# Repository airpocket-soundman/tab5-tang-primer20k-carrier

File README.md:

# Tab5 × Tang Primer 20K 接続キャリア基板

2026-11-08：FPGA単独推論の実験版4E30を追加。FPGA内RV32IMCが量子化・正規化等を処理し、共通INT8 MACが積和演算を担当する。Tab5/P4はモデル・画像の搬入と表示のみ。全RT-DETR649演算は実RV32 ISA試験で完走し、実機では14整数のCPU＋MAC試験に合格。**全モデルの実機完走・速度は未確認**。[自律実行仕様](docs/NPU_AUTONOMOUS_V1.md)、[ISA検証](docs/NPU_AUTONOMOUS_RV32_ISA_2026-11-08.md)を参照。Linux/MeOS loaderは未実装。

2026-11-07：NPU DDR診断版4E21で、YOLO S256の32MiB超え実行と、学習済みDeiT-tiny全12ブロック・74行列演算の実機実行を確認。Transformerの1000出力は同じP4の独立CPU整数計算と全ビット一致した。既存の積和回路を使い、ピン・通信コマンドの変更はない。非線形演算等はP4が担当し、Linux/MeOSへのホスト実装移植とSTA収束は未完了。[Transformer実機記録](docs/NPU_Transformer_実機検証_2026-11-07.md)、[DDR MatMul検証](docs/NPU_DDR_MatMul_検証_2026-11-07.md)を参照。

2026-11-06の保存点：GPU全8シーン/TX40・RX16検証記録とMEM DMA検証・復元資料をmainへ統合。[当時の現在地・全host適合範囲・整理方針](docs/INTEGRATION_2026-11-06.md)を参照。RX20、長時間soak、DDR付きGFXは未完了。

M5Stack Tab5のM5-BusとTang Primer 20K Coreを接続する専用キャリア基板の設計リポジトリです。

## 状態

2026-11-05のジャンパ接続GFX実機では、全8シーン×3負荷の640×360画像照合とFlow継続照合に合格。
[全8シーンの仕様・実績・失敗候補](docs/GFX全8シーン拡張_2026-11-05.md)を参照。
現行SLogic配線はCLK=D7／DIR=D6／READY=D4／DATA0～7=D15～D8で、
[9往復CRC照合による全チャンネル特定記録](fpga/validation/probe-map-complete-2026-11-05/manifest.json)を保存した。
これはジャンパ実機の結果であり、下記キャリア基板の製造・検証完了を意味しない。

フル125×78mmと廉価版A99×78mmの設計レビュー用データがあります。未製造・未実機検証です。

**実装仕様変更（2026-10-26）：** 片面SMTを優先し、主電源スイッチと旧FPGA専用停止SW3を省くr4へ変更しました。Tab5用J3はLCSC別購入・手はんだです。設計側PCB DRC違反・ERCエラーは両版とも0です。ERC警告はフル版163件、廉価版164件（ライブラリシンボル不一致160／161件と孤立ピンラベル3件）あります。EasyEDA反映・再計算完了のため見積もり用で、製造リリースは未完了です。[現在の仕様](spark/single-sided-r4/README.md)。

## 保持している従来版

125×78mmの従来版と廉価版A/B/Cは保存しています。既存の製造・解析記録は各版のものです。Spark主電源改訂の検証結果ではありません。

- [廉価版3案の一覧](variants/README.md)
- [3案の共通設計仕様](variants/DESIGN_SPEC.md)
- [廉価版レポート](site/lite-variants.html)

## 設計の起点

[共通ハードウェア仕様・設計チェック項目](docs/ESP32P4_FPGA_共通ハード仕様.md)

- 初期通信：8bit PARLIOと制御線。将来16bit化を検討。
- 電源：外部約12VからTab5 HVINへ供給し、FPGAには独立した12V→5V DC-DCで供給。
- 共通GNDとし、Tab5の5VレールとFPGA用5Vは直結しない。
- DDR3はCore搭載のものを使用する。

GPIO割り当て・コネクタ・電源条件は暫定です。一次資料との照合、I/O電圧・競合・起動状態・逆給電の確認を行い、仕様のチェック項目を完了してから製造に進みます。

## FPGAデバイスと利用するホスト

Tab5側のソフト実装は[ホストソフト開発ガイド](docs/Tab5ホストソフト開発ガイド.md)を参照してください。

ジャンパ線で先に通信・描画を試す場合は[Dock接続とTab5内蔵LCDのGFX試験手順](docs/Dockジャンパ_GFXテスト手順.md)を参照。Dock用top、32×32 RGB565描画診断、読み戻し照合とホスト側表示経路を開発しています。RTL試験とOSSでの合成・配置配線・ビットストリーム生成は成功、Gowin EDAと実機は未検証です。

本リポジトリは、キャリア基板と、その上で動くFPGAデバイス（全ビットストリーム）を一元管理します。ホストOSの各リポジトリは本リポジトリの仕様を参照してホスト側を開発します。[リポジトリ分担と参照ルール](docs/リポジトリ分担と参照ルール.md)、[FPGAデバイス構成](docs/FPGAデバイス構成_ビットストリームと機能.md)、[fpga/](fpga/README.md)を参照してください。

| リポジトリ | ホスト側の役割 |
|---|---|
| [tab5-linux-fpga](https://github.com/airpocket-soundman/tab5-linux-fpga) | NOMMU Linux本体、FPGA通信ドライバ、Device Tree、ユーザ空間ツール |
| [tab5-meos-fpga](https://github.com/airpocket-soundman/tab5-meos-fpga) | MeOSのFPGAドライバ（HAL/LL PARLIO）、GUI統合 |
| [tab5-fpga-gpu](https://github.com/airpocket-soundman/tab5-fpga-gpu) | ESP-IDFのホスト実装、ベンチマーク（GPU LAB）、モデル評価 |
| [esp32p4-linux-fpga-memory](https://github.com/airpocket-soundman/esp32p4-linux-fpga-memory) | Linux外部メモリ研究の計画・評価 |

FPGAの機能（GFX、NPU、HDMI、RAMdisk）はどのホストOSからも使う前提です。ビットストリームは機能別に分け、同時搭載は計測で問題がない組合せに限ります。

Linux側では双方向のコマンド・データ転送、128MB DDR3全域への分割読み書き、フロー制御・通知とエラー検出を支えます。描画用途では描画コマンド送信と完成フレーム受信を支え、640×360 RGB565・30FPSの目標に対して、フレーム本体だけで約13.8MB/sを要する受信経路を評価します。DMA対応と実効帯域は未検証であり、性能を保証するものではありません。

共通仕様・デバイス仕様の更新は本リポジトリを起点とし、ホスト側リポジトリに収録した仕様コピーへ反映してください。

## Spark応募用の独立フル機能版

従来設計とA/B/Cの計画を保持し、125×78mm・HDMI・USB PD付きの別版を [spark/](spark/README.md) で開発しています。KiCadで設計・解析してEasyEDAへ移植し、PCBAを優先、手はんだ品もLCSC調達を優先し、適合品をLCSCで調達できない場合のみ秋月電子へ集約します。[検証状況と残件](spark/design/VERIFICATION_STATUS.md)を確認してください。現行の製造データは見積・レビュー用です。

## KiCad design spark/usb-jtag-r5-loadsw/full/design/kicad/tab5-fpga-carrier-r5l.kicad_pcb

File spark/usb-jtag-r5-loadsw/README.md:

# r5l：SW4を信号専用にして、+5VをPMOSのロードスイッチで通す変種（PoC・発注候補）

2026-11-06。**実機未検証。リリースではありません。** r5s（`../usb-jtag-r5-switch/`）の派生で、r5s、r5、r5c、r4 のファイルは変更していません。

## 何を変えたか

- r5sでは、SW4（G-Switch SS-23D03-G080）が+5Vレールの電流を通していた。この部品の電流定格は、メーカーのデータシートで **0.3A・50V DC**（LCSCの掲載値1Aと食い違う）。
- r5lでは、SW4は**信号だけ**（ゲート駆動とCFG1）。+5Vの電流は、背中合わせのPMOS（AO3401A）が通す。
  - RUN経路 Q11・Q12（BUCK_5V → +5V）、PGM経路 Q13・Q14（VBUS_PD → +5V）。
  - PGM経路の過電圧ガード Q15・D12・R95（VBUS_PDが約7Vを超えたら、PGM経路をオフにする）。
- 追加11部品（Q11〜Q15、D12、R91〜R95）。基板の部品位置・配線の他の部分は、r5sのまま。

詳しい検討・SPICE結果・未確認事項は `../../docs/r5s_SW4ロードスイッチ式の検討_2026-11-06.md`。

## 中身

| 場所 | 内容 |
|---|---|
| `full/design/kicad/` | KiCadの回路図・基板・BOM・回路契約（`circuit-contract.json`）。`gen/` に生成スクリプト |
| `full/design/kicad/gen/add_loadsw.py` | r5sの基板から、r5lの基板を作る（部品の配置探索＋配線）。`loadsw_routes.py` が配線の指定 |
| `sim-spice/` | ロードスイッチのngspice検証（`run_all.py`、結果は `results.json`）。汎用モデル |
| `verify_design.py` | 回路図のネットリスト検査（SW4の位置モデル、ロードスイッチの接続、SW4が電源を通さないこと、ERC・DRC） |
| `order/` | JLCPCB向けの発注候補データ（ガーバー、BOM、CPL）と、`README.md`（未解決事項） |
| `review/` | 確認用の画像（3D） |

## 検証したこと

- ERCエラー0、PCB DRC違反0、未配線0（`full/design/kicad/sim/`）。
- 回路図と基板のネット照合: 761ピン、不一致0。r5sとの基板の差分は、SW4の電源配線の削除24点と、SW4の3ピンのネット変更だけ。
- `verify_design.py`: PASS（SW4のスライダ位置モデル、ロードスイッチの接続、危険な組合せなし）。
- SPICE（汎用モデル）: RUN／PGM／OFF、DCのみ、VBUS 12V誤使用（+5V＝0V）、5.5V給電で誤遮断なし。+5Vのピークは、ランプで5.5〜7.7V。

## 既知の制約（PoCとして受け入れる範囲）

2026-11-07の再監査（`../../docs/r5l基板再監査_2026-11-07.md`）を受けて、次を明記する。

1. **過電圧ガードは、定格内に収める保護ではない。** VBUSがランプで上がるとき、+5Vのピークは最大約7.7Vで、**3.3V LDO（U3 TLV1117LV33）の絶対最大入力6V（動作範囲は2〜5.5V）を超える**。ガードは、12VのままPGMへ切り替えるなどの誤使用で、被害を小さくする「保険」にとどまる。約7Vで切る6.2Vゼナー方式は、PDの5V許容（5.5V）を通しつつ5.5V超を切る、という窓に原理的に合わない。回路は、PoCとして作り直さない。
2. **運用ルール:** RUN／OFF／PGM（SW4）と、JP3、JP1の切り替えは、**電源アダプタとUSB-Cを外した無電源の状態で行う**（シルクの `POWER OFF!` のとおり）。通電中のモード切替は、保護の対象に入れていない。
3. **USB D+／D−:** 差動ペアとして並べて配線していない。経路長はD+約17.0〜17.5mm、D−約25.1〜27.0mm（差約8mm）。90Ωの積層設計も未確認。ハイスピード動作は、実機で確認する（ハイスピードで認識できない場合は、フルスピードの動作を確認する）。

### Core（Tang Primer 20K）のI/O電源（VCCO）の条件

このキャリアは、SODIMMの164・166（Bank 0/1の外部VCCO）と、170・174（Bank 7の外部VCCO）を**未接続**にしている。一方で、Bank 0、1、7のピンを使う（Bank 7には、LINKの F_D5、F_D6、F_D7、F_DIR などが載る）。

- Core回路図の読み取り（`../../docs/reference/README.md`、`../../docs/Dockジャンパ試験_配線とFPGA構成_2026-10-28.md`）では、**既定のCoreは R5（Bank 0/1）と R9（Bank 7）が付いていて、VCCOはCore内部の3.3V**。この場合、164・166・170・174を未接続にしても、該当バンクは3.3Vで動く。
- **R6（Bank 0/1の外部選択）または R13（Bank 7の外部選択）が付いているCoreでは、キャリアがVCCOを供給しない限り、該当バンクが無給電になる。**
- 公式Dockは、164・166に3.3Vを接続し、170・174は未接続にしている（Bank 7は、Dock上でR9の実装を確認できないため、使わない運用）。**Dockで動いたことは、このキャリアでBank 7が動く証拠にならない。**

**このキャリアで使うCoreの条件（組立・受入）:**
1. R5とR9が実装されていて、R6とR13が実装されていないこと。Coreを挿す前に、実物で目視（または抵抗の導通）で確認する。
2. Coreに5Vだけを与えて通電した状態（キャリアには挿さない、またはキャリアの5Vだけ入れる）で、**Core基板上の VCCO7 のノード（R9またはR13の、FPGA側のパッド、またはFPGA近くのVCCO7のデカップリング容量）とGNDの間の電圧が3.3Vであること**を確認する。**SODIMMの170・174の電圧では、確認できない**（R13が実装されていなければ、170・174はCoreの内部にどこにもつながらず、電圧が出ない。R9実装・R13非実装が、この基板の想定する正しい状態）。同様に Bank 0/1 は、R5またはR6のFPGA側パッドで確認する。
3. 確認できていない間は、「Bank 7（F_D5〜F_D7、F_DIR、GPIO0〜4、F_LED0〜1 など）の動作は未確認」として扱う。

この条件は、実機のCoreで確認するまで、**未確認**である。

## 再現

```
"C:/Program Files/KiCad/10.0/bin/python.exe" full/design/kicad/gen/add_loadsw.py      # r5s基板 -> r5l基板
python full/design/kicad/gen/build_r5.py                                               # 回路図・BOM（r5lのコピー内でだけ実行）
python verify_design.py
python sim-spice/run_all.py
```

発注データの再生成は、`order/README.md` の「再生成」を参照。

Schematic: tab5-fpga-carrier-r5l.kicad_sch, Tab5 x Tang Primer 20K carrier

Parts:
C1: 100u/35V; CP_Elec_6.3x7.7; LCSC C2983388
C2: 1u/50V; C_0603_1608Metric; LCSC C15849
C3: 10n; C_0603_1608Metric; LCSC C57112
C4, C5: 10u/50V; C_1206_3216Metric; LCSC C13585
C6: 100n/50V; C_0603_1608Metric; LCSC C14663
C7: 220u/10V POSCAP; CP_EIA-7343-40_Kemet-Y; LCSC C242173
C8, C9: 47u/10V; C_1206_3216Metric; LCSC C96123; not fitted
C10: 10u/16V; C_1206_3216Metric; LCSC C13585
C11: 22u/10V; C_1206_3216Metric; LCSC C12891
C12, C13, C14, C15, C16, C17, C18, C19: 100n; C_0402_1005Metric; LCSC C1525
C20, C21, C22, C23, C24, C85, C88, C89, C90, C91, C92, C93, C94, C95, C97: 100n; C_0603_1608Metric; LCSC C14663
C86, C87: 33p; C_0603_1608Metric; LCSC C1663
C96: 4.7u; C_0603_1608Metric; LCSC C19666
D1, D2, D4: SS54; D_SMA; LCSC C22452
D3: SMBJ15A; D_SMB; LCSC C699013
D5, D6, D7, D8: LED; LED_0603_1608Metric; LCSC C2286
D10, D11: PESD5V0U1BL; D_SOD-882; LCSC C3001955
D12: BZT52C6V2; D_SOD-123; LCSC C19077403
F1: PTC 3A hold; Fuse_1812_4532Metric; LCSC C47002391
F2: PTC 500mA; Fuse_1206_3216Metric; LCSC C315893
H1, H2, H3, H4, H5, H6: M3; MountingHole_3.2mm_M3
J1: DC-005-5A-2.0; BarrelJack_XKB_C381116; LCSC C381116
J2: TYPE-C-31-M-12 USB2 + PD; USB_C_Receptacle_HRO_TYPE-C-31-M-12; LCSC C165948
J3: 2.54-2*15P; PinHeader_2x15_Tab5_Bottom; LCSC C56496
J4: SOCKET XDAP-4042044-20401; DDR3_XDAP_4042044_20401; LCSC C22471982
J5: HDMI OUT; HDMI_A_Molex_208658-1001_Horizontal; LCSC C916313
J6: PMOD1; PinHeader_2x06_P2.54mm_Vertical; not fitted
J7: PMOD2; PinHeader_2x06_P2.54mm_Vertical; not fitted
J8: GPIO pads; PinHeader_1x09_P2.54mm_Vertical; not fitted
JP1: BUS ARM; PinHeader_1x03_P2.54mm_Vertical; LCSC C49257
JP3: MODE TAB5; PinHeader_1x03_P2.54mm_Vertical; LCSC C49257
L1: 15u/4A; L_Bourns_SRR1260; LCSC C2041333
Q1, Q2, Q3, Q4, Q7, Q8: 2N7002; SOT-23; LCSC C8545
Q5: MMBT3904; SOT-23; LCSC C20526
Q11, Q12, Q13, Q14, Q15: AO3401A; SOT-23; LCSC C15127
R1, R2, R5: 0R; R_0603_1608Metric; LCSC C21189
R4, R17, R18, R25: 0R; R_0603_1608Metric; LCSC C21189; not fitted
R6, R36, R37, R52, R82, R86, R87, R90, R95: 10k; R_0603_1608Metric; LCSC C25804
R7: 3.24k; R_0603_1608Metric; LCSC C22994
R8, R41, R47, R48, R73, R74, R88, R91, R93: 100k; R_0603_1608Metric; LCSC C25803
R9: 15k; R_0603_1608Metric; LCSC C22809
R10, R11, R12, R13, R14, R15, R16, R19, R20, R21, R22, R23, R24, R26, R27: 680R; R_0603_1608Metric; LCSC C23228
R28, R29, R32, R33, R34, R35: 499R; R_0603_1608Metric; LCSC C23065
R30, R31: 499R; R_0402_1005Metric; LCSC C4125
R38, R39: 2.2k; R_0603_1608Metric; LCSC C4190
R40, R51: 47k; R_0603_1608Metric; LCSC C25819
R42, R43, R44, R45: 1k; R_0603_1608Metric; LCSC C21190
R46: 22k; R_0603_1608Metric; LCSC C31850
R81: 12k 1%; R_0603_1608Metric; LCSC C22790
R83, R84, R85: 33R; R_0603_1608Metric; LCSC C23140
R89: 1M; R_0603_1608Metric; LCSC C22935
R92, R94: 4.7k; R_0603_1608Metric; LCSC C23162
SW1, SW2: TS-1102S-B-D-B; SW_XKB_TS1102S_C480272; LCSC C480272
SW4: SS-23D03-G080; SW_SLIDE_DP3T_SS-23D03-G080; LCSC C2848921
U1: CH224A; SSOP-10-1EP_3.9x4.9mm_P1mm_EP2.1x3.3mm; LCSC C42459160
U2: TPS5430DDAR; TI_SO-PowerPAD-8_ThermalVias; LCSC C9864
U3: TLV1117LV33DCYR; SOT-223-3_TabPin2; LCSC C15578
U4, U5, U6: RCLAMP0524P; DFN2510-10L_RCLAMP0524P; LCSC C293965
U7, U8: SN74CB3Q3245PWR; TSSOP-20_4.4x6.5mm_P0.65mm; LCSC C470961
U9: TPS3839G33DBZR; SOT-23; LCSC C485802
U10: TPS3839K50DBZR; SOT-23; LCSC C702204
U17: FT232HL-REEL; LQFP-48_7x7mm_P0.5mm; LCSC C51997
U19: SN74LVC125APWR; TSSOP-14_4.4x5mm_P0.65mm; LCSC C7813
Y1: 12MHz CL20pF 20ppm X322512MSB4SI; Crystal_SMD_SeikoEpson_FA238-4Pin_3.2x2.5mm; LCSC C9002

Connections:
+3V3: C11.1, C20.1, C21.1, C97.1, J6.11, J6.12, J7.11, J7.12, J8.1, Q1.1 (G), Q2.1 (G), R36.1, R37.1, R46.1, R51.1, R87.1, U3.2 (VO), U7.20 (VCC), U8.20 (VCC), U19.14 (VCC)
+5V: C10.1, C23.1, C95.1, F2.1, J4.4 (+5V), J4.5 (+5V), J4.6 (+5V), J4.7 (+5V), Q12.3 (D), Q14.3 (D), U3.3 (VI), U10.3 (VDD), U17.40 (VREGIN)
BUCK_5V: C7.1, C8.1, C9.1, L1.2, Q11.3 (D), R6.1
BUCK_BOOT: C3.1, U2.1 (BOOT)
BUCK_EN: R8.2, R9.1, U2.5 (EN)
BUCK_FB: R6.2, R7.1, U2.4 (VSENSE)
BUCK_PH: C3.2, D4.1 (K), L1.1, U2.8 (PH)
BUS_ARM: JP1.2, Q3.1 (G), R47.1
BUS_OE_MID: Q3.2 (S), Q4.3 (D)
BUS_OE_N: Q3.3 (D), R46.2, U7.19 (~OE), U8.19 (~OE)
CC1: J2.A5 (CC1), U1.7 (CC1)
CC2: J2.B5 (CC2), U1.6 (CC2)
CORE_PGOOD: Q4.1 (G), R48.1, U10.2 (~RESET)
DBG_3V3: C88.1, C89.1, C90.1, C91.1, C92.1, C96.1, R82.1, R90.1, U17.3 (VPHY), U17.8 (VPLL), U17.12 (VCCIO), U17.24 (VCCIO), U17.39 (VCCD), U17.46 (VCCIO)
DBG_TCK: U17.13 (ADBUS0), U19.2 (A1)
DBG_TDI: U17.14 (ADBUS1), U19.5 (A2)
DBG_TDO: U17.15 (ADBUS2), U19.11 (Y4)
DBG_TMS: U17.16 (ADBUS3), U19.9 (A3)
DC_IN: D1.2 (A), F1.2
DC_RAW: F1.1, J1.1
FT_1V8A: C93.1, U17.37 (VCCA)
FT_1V8D: C94.1, U17.38 (VCCCORE)
FT_REF: R81.1, U17.5 (REF)
FT_RESET_N: C85.1, Q8.3 (D), R82.2, U17.34 (~RESET)
F_AUX0: J4.73 (F_AUX0), R11.2
F_AUX1: J4.79 (F_AUX1), R14.2
F_AUX2: J4.95 (F_AUX2), R19.2
F_AUX3: J4.97 (F_AUX3), R20.2
F_BTN0: J4.74 (F_BTN0), SW1.1
F_CLK: J4.52 (F_CLK), R10.2
F_D0: J4.77 (F_D0), R13.2
F_D1: J4.83 (F_D1), R15.2
F_D2: J4.85 (F_D2), R16.2
F_D3: J4.103 (F_D3), R22.2
F_D4: J4.101 (F_D4), R21.2
F_D5: J4.109 (F_D5), R24.2
F_D6: J4.107 (F_D6), R23.2
F_D7: J4.115 (F_D7), R26.2
F_DIR: J4.119 (F_DIR), R27.2
F_EXT35: J4.113 (F_EXT35), R25.2
F_EXT37: J4.89 (F_EXT37), R17.2
F_EXT38: J4.91 (F_EXT38), R18.2
F_HPD: J4.30 (F_HPD), R52.2
F_HSCL: J4.36 (F_HSCL), Q1.2 (S), R36.2
F_HSDA: J4.34 (F_HSDA), Q2.2 (S), R37.2
F_LED0: J4.146 (F_LED0), R42.1
F_LED1: J4.148 (F_LED1), R43.1
F_LED2: J4.152 (F_LED2), R44.1
F_LED3: J4.154 (F_LED3), R45.1
F_RDY: J4.75 (F_RDY), R12.2
GND: C1.2, C2.2, C4.2, C5.2, C6.2, C7.2, C8.2, C9.2, C10.2, C11.2, C20.2, C21.2, C22.2, C23.2, C24.2, C85.2, C86.2, C87.2, C88.2, C89.2, C90.2, C91.2, C92.2, C93.2, C94.2, C95.2, C96.2, C97.2, D3.2 (A2), D4.2 (A), D5.1 (K), D6.1 (K), D7.1 (K), D8.1 (K), D10.2 (A2), D11.2 (A2), D12.2 (A), J1.2, J1.3, J2.A1 (GND), J2.A12 (GND), J2.B1 (GND), J2.B12 (GND), J2.SH (SHIELD), J3.1, J3.3, J3.5, J4.2 (GND), J4.3 (GND), J4.8 (GND), J4.9 (GND), J4.13 (GND), J4.14 (GND), J4.19 (GND), J4.20 (GND), J4.25 (GND), J4.26 (GND), J4.31 (GND), J4.32 (GND), J4.37 (GND), J4.38 (GND), J4.43 (GND), J4.48 (GND), J4.49 (GND), J4.54 (GND), J4.55 (GND), J4.60 (GND), J4.61 (GND), J4.66 (GND), J4.71 (GND), J4.72 (GND), J4.127 (GND), J4.128 (GND), J4.133 (GND), J4.134 (GND), J4.138 (GND), J4.139 (GND), J4.144 (GND), J4.145 (GND), J4.150 (GND), J4.151 (GND), J4.155 (GND), J4.156 (GND), J4.161 (GND), J4.162 (GND), J4.168 (GND), J4.172 (GND), J4.173 (GND), J4.178 (GND), J4.179 (GND), J4.184 (GND), J4.185 (GND), J4.189 (GND), J4.190 (GND), J4.195 (GND), J4.196 (GND), J4.MP, J5.2 (D2S), J5.5 (D1S), J5.8 (D0S), J5.11 (CKS), J5.17 (GND), J5.SH, J6.9, J6.10, J7.9, J7.10, J8.2, Q4.2 (S), Q5.2 (E), Q7.2 (S), Q8.2 (S), R4.2, R5.2, R7.2, R9.2, R28.2, R29.2, R30.2, R31.2, R32.2, R33.2, R34.2, R35.2, R41.2, R47.2, R48.2, R74.2, R81.2, R86.2, R89.2, SW1.2, SW2.2, SW4.4 (A_COM), SW4.8 (B_RUN), SW4.9 (SH), SW4.10 (SH), U1.11 (GND), U2.6 (GND), U2.9 (GNDPAD), U3.1 (GND), U4.3 (GND), U4.8 (GND), U5.3 (GND), U5.8 (GND), U6.3 (GND), U6.8 (GND), U7.10 (GND), U8.10 (GND), U9.1 (GND), U10.1 (GND), U17.4 (AGND), U17.9 (AGND), U17.10 (GND), U17.11 (GND), U17.22 (GND), U17.23 (GND), U17.35 (GND), U17.36 (GND), U17.41 (AGND), U17.42 (TEST), U17.47 (GND), U17.48 (GND), U19.1 (~OE1), U19.4 (~OE2), U19.7 (GND), U19.10 (~OE3), U19.13 (~OE4), Y1.2 (G), Y1.4 (G)
GPIO0: J4.125 (GPIO0), J8.3
GPIO1: J4.129 (GPIO1), J8.4
GPIO2: J4.131 (GPIO2), J8.5
GPIO3: J4.176 (GPIO3), J8.6
GPIO4: J4.180 (GPIO4), J8.7
GPIO5: J4.182 (GPIO5), J8.8
GPIO6: J4.186 (GPIO6), J8.9
HDMI_5V: F2.2, J5.18 (+5V), R38.1, R39.1, U6.2 (IO2), U6.9 (NC)
HDMI_CKN: C19.1, J4.142 (HDMI_CKN)
HDMI_CKN_C: C19.2, J5.12 (CK-), R35.1, U5.5 (IO4), U5.6 (NC)
HDMI_CKP: C18.1, J4.140 (HDMI_CKP)
HDMI_CKP_C: C18.2, J5.10 (CK+), R34.1, U5.4 (IO3), U5.7 (NC)
HDMI_D0N: C17.1, J4.132 (HDMI_D0N)
HDMI_D0N_C: C17.2, J5.9 (D0-), R33.1, U5.2 (IO2), U5.9 (NC)
HDMI_D0P: C16.1, J4.130 (HDMI_D0P)
HDMI_D0P_C: C16.2, J5.7 (D0+), R32.1, U5.1 (IO1), U5.10 (NC)
HDMI_D1N: C15.1, J4.70 (HDMI_D1N)
HDMI_D1N_C: C15.2, J5.6 (D1-), R31.1, U4.5 (IO4), U4.6 (NC)
HDMI_D1P: C14.1, J4.68 (HDMI_D1P)
HDMI_D1P_C: C14.2, J5.4 (D1+), R30.1, U4.4 (IO3), U4.7 (NC)
HDMI_D2N: C13.1, J4.58 (HDMI_D2N)
HDMI_D2N_C: C13.2, J5.3 (D2-), R29.1, U4.2 (IO2), U4.9 (NC)
HDMI_D2P: C12.1, J4.56 (HDMI_D2P)
HDMI_D2P_C: C12.2, J5.1 (D2+), R28.1, U4.1 (IO1), U4.10 (NC)
HDMI_HPD: J5.19 (HPD), R40.1, U6.5 (IO4), U6.6 (NC)
HDMI_SCL: J5.15 (SCL), Q1.3 (D), R38.2, U6.4 (IO3), U6.7 (NC)
HDMI_SDA: J5.16 (SDA), Q2.3 (D), R39.2, U6.1 (IO1), U6.10 (NC)
HPD_B: Q5.1 (B), R40.2, R41.1
HPD_BUF: C24.1, Q5.3 (C), R51.2, R52.1
ISO_AUX0: R11.1, U7.17 (B2)
ISO_AUX1: R14.1, U7.14 (B5)
ISO_AUX2: R19.1, U7.11 (B8)
ISO_AUX3: R20.1, U8.18 (B1)
ISO_CLK: R10.1, U7.18 (B1)
ISO_D0: R13.1, U7.15 (B4)
ISO_D1: R15.1, U7.13 (B6)
ISO_D2: R16.1, U7.12 (B7)
ISO_D3: R22.1, U8.16 (B3)
ISO_D4: R21.1, U8.17 (B2)
ISO_D5: R24.1, U8.14 (B5)
ISO_D6: R23.1, U8.15 (B4)
ISO_D7: R26.1, U8.13 (B6)
ISO_DIR: R27.1, U8.12 (B7)
ISO_RDY: R12.1, U7.16 (B3)
JTAG_TCK: J4.149 (JTAG_TCK), R83.2, R86.1
JTAG_TCK_PRE: R83.1, U19.3 (Y1)
JTAG_TDI: J4.153 (JTAG_TDI), R84.2
JTAG_TDI_PRE: R84.1, U19.6 (Y2)
JTAG_TDO: J4.147 (JTAG_TDO), U19.12 (A4)
JTAG_TMS: J4.143 (JTAG_TMS), R85.2, R87.2
JTAG_TMS_PRE: R85.1, U19.8 (Y3)
LED0_A: D5.2 (A), R42.2
LED1_A: D6.2 (A), R43.2
LED2_A: D7.2 (A), R44.2
LED3_A: D8.2 (A), R45.2
LS_KG: D12.1 (K), Q15.1 (G), R95.2
LS_SCP: Q13.2 (S), Q14.2 (S), Q15.2 (S), R93.1, R95.1
LS_SCR: Q11.2 (S), Q12.2 (S), R91.1
M_AUX0: J3.4, U7.3 (A2)
M_AUX1: J3.10, U7.6 (A5)
M_AUX2: J3.16, U7.9 (A8)
M_AUX3: J3.15, U8.2 (A1)
M_CLK: J3.2, U7.2 (A1)
M_D0: J3.7, U7.5 (A4)
M_D1: J3.9, U7.7 (A6)
M_D2: J3.11, U7.8 (A7)
M_D3: J3.19, U8.4 (A3)
M_D4: J3.20, U8.3 (A2)
M_D5: J3.21, U8.6 (A5)
M_D6: J3.22, U8.5 (A4)
M_D7: J3.23, U8.7 (A6)
M_DIR: J3.26, U8.8 (A7)
M_EXT35: J3.24, R25.1
M_EXT37: J3.14, R17.1
M_EXT38: J3.13, R18.1
M_RDY: J3.8, U7.4 (A3)
P1_0: J4.76 (P1_0), J6.1
P1_1: J4.84 (P1_1), J6.3
P1_2: J4.90 (P1_2), J6.5
P1_3: J4.121 (P1_3), J6.7
P1_4: J4.78 (P1_4), J6.2
P1_5: J4.86 (P1_5), J6.4
P1_6: J4.92 (P1_6), J6.6
P1_7: J4.123 (P1_7), J6.8
P2_0: J4.40 (P2_0), J7.1
P2_1: J4.44 (P2_1), J7.3
P2_2: J4.50 (P2_2), J7.5
P2_3: J4.62 (P2_3), J7.7
P2_4: J4.42 (P2_4), J7.2
P2_5: J4.46 (P2_5), J7.4
P2_6: J4.80 (P2_6), J7.6
P2_7: J4.64 (P2_7), J7.8
PD_CFG1: R73.2, SW4.5 (B_COM), U1.9 (CFG1)
PD_CFG2: R5.1, U1.2 (CFG2/SCL)
PD_CFG3: R4.1, U1.3 (CFG3/SDA)
PD_PG: U1.10 (PG)
PD_VBUS_S: R2.2, U1.8 (VBUS)
PD_VDD: C2.1, R1.2, R73.1, U1.1 (VHV)
PGM_G: Q13.1 (G), Q14.1 (G), Q15.3 (D), R93.2, R94.1
RUN_G: Q11.1 (G), Q12.1 (G), R91.2, R92.1
SW_PGM: R94.2, SW4.3 (A_PGM)
SW_RUN: R92.2, SW4.1 (A_RUN)
TAB_3V3: C22.1, J3.12, U9.3 (VDD)
TAB_HVIN: J3.25, J3.27, J3.29, JP3.2, R74.1
TAB_PGOOD: JP1.1, U9.2 (~RESET)
TAB_RST: J3.6, SW2.1
TAB_SCL: J3.18
TAB_SDA: J3.17
USB_ABSENT: Q7.3 (D), Q8.1 (G), R90.2
USB_DM: D11.1 (A1), J2.A7 (D-), J2.B7 (D-), U17.6 (DM)
USB_DP: D10.1 (A1), J2.A6 (D+), J2.B6 (D+), U17.7 (DP)
VBUS_GATE: Q7.1 (G), R88.2, R89.1
VBUS_PD: D2.2 (A), J2.A4 (VBUS), J2.A9 (VBUS), J2.B4 (VBUS), J2.B9 (VBUS), Q13.3 (D), R1.1, R2.1, R88.1
VIN: C1.1, C4.1, C5.1, C6.1, D1.1 (K), D2.1 (K), D3.1 (A1), JP3.1, R8.1, U2.7 (VIN)
XTAL_IN: C86.1, U17.1 (XCSI), Y1.1
XTAL_OUT: C87.1, U17.2 (XCSO), Y1.3

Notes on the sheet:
POWER INPUT: DC barrel + USB-C PD (OR) -> VIN
USB-C PD sink (CH224A, 12V request)
VIN -> BUCK_5V (r4 TPS5430 retained)
+5V -> +3V3 (peripherals)
M5-BUS header (Tab5-facing side)
Power-off bus isolation + 33R (M=Tab5, ISO=switch, F=FPGA)
HDMI OUT connector + DDC/HPD level shift + ESD
HDMI TMDS 499R bias, ESD
HDMI TMDS AC coupling caps
PMOD x2
FPGA JTAG header
Spare FPGA I/O pads
LEDs / buttons
Mounting holes (Tab5 M3)
Tang Primer 20K Core SODIMM socket (pin names = nets)
R5L: SW4 slide switch (signals only) 1=RUN 3=PROGRAM 2=OFF; +5V through load switches Q11-Q15 (P-MOS); JP3 still manual; change only UNPOWERED
R5 MANUAL: FT232H USB-JTAG, NO EEPROM; direct SODIMM JTAG143/147/149/153
Nets: GND +5V +3V3 are power symbols; all other nets connect by label.
M5-Bus pins 28 (5V) and 30 (BAT) are intentionally NOT connected (Tab5 outputs).
Do NOT tie Tab5 5V to the FPGA 5V rail. GND is common.

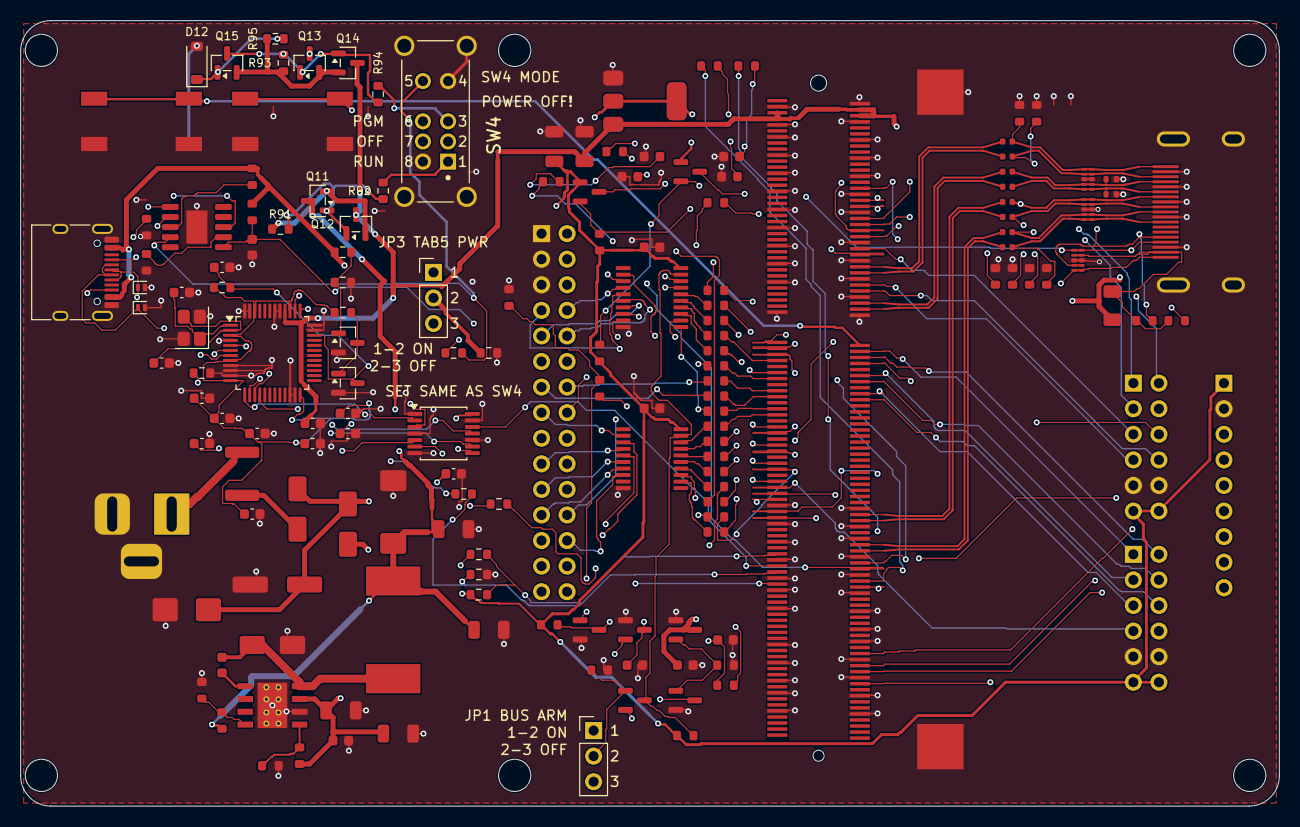
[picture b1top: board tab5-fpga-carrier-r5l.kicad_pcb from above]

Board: 4 copper layers, 125.0 x 78.0 mm, 161 parts (1 on the bottom side), 164 nets.

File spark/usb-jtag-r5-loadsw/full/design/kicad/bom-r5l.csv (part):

Reference,Value,Footprint,DNP,LCSC,Comment
J1,DC-005-5A-2.0,carrier:BarrelJack_XKB_C381116,False,C381116,LCSC/JLC wave-solder candidate; center-positive stabilized12V only; XKB drawing A1 2025-04-22. 5A connector rating is not board current rating. Verify actual power plug fit.
F1,PTC 3A hold,Fuse:Fuse_1812_4532Metric,False,C47002391,
D1,SS54,Diode_SMD:D_SMA,False,C22452,reverse-polarity + OR (DC jack)
D2,SS54,Diode_SMD:D_SMA,False,C22452,OR (USB-C PD)
D3,SMBJ15A,Diode_SMD:D_SMB,False,C699013,"YANGJIE 15V standoff, 24.4V specified clamp; regulated 12V PoC input only"
C1,100u/35V,Capacitor_SMD:CP_Elec_6.3x7.7,False,C2983388,
J2,TYPE-C-31-M-12 USB2 + PD,Connector_USB:USB_C_Receptacle_HRO_TYPE-C-31-M-12,False,C165948,"USB2 data and PD; PROGRAM strap requests5V; no automatic power selector LCSC C165948 (HRO TYPE-C-31-M-12), extended; shell stakes are through-hole (hybrid assembly)."
U1,CH224A,Package_SO:SSOP-10-1EP_3.9x4.9mm_P1mm_EP2.1x3.3mm,False,C42459160,"WCH CH224A (ESSOP-10, pin-compatible with CH224K), 12V request: CFG1=0 CFG2=0 CFG3=1(internal PU). Pin 1 = VHV, pin 8 VBUS must be shorted to VHV (R1, R2 = 0R). CFG1 max 3.8V: only R73 (100k to VHV) may pull it up."
R1,0R,Resistor_SMD:R_0603_1608Metric,False,C21189,0R for the CH224A: VHV supply directly from VBUS (CH224K needed 10k / 1k here). WCH CH224 datasheet V2.1 chapter 7.2.
C2,1u/50V,Capacitor_SMD:C_0603_1608Metric,False,C15849,
R2,0R,Resistor_SMD:R_0603_1608Metric,False,C21189,0R for the CH224A: VBUS detect pin shorted to VHV (CH224K needed 10k / 1k here). WCH CH224 datasheet V2.1 chapter 7.2.
R4,0R,Resistor_SMD:R_0603_1608Metric,True,C21189,Must remain DNP: CFG3 internal pull-up for 12V request
R5,0R,Resistor_SMD:R_0603_1608Metric,False,C21189,"Fitted: CFG2 low, CFG1 low, CFG3 high -> 12V"
U2,TPS5430DDAR,Package_SO:TI_SO-PowerPAD-8_ThermalVias,False,C9864,
C3,10n,Capacitor_SMD:C_0603_1608Metric,False,C57112,
L1,15u/4A,Inductor_SMD:L_Bourns_SRR1260,False,C2041333,
D4,SS54,Diode_SMD:D_SMA,False,C22452,catch diode
R6,10k,Resistor_SMD:R_0603_1608Metric,False,C25804,
R7,3.24k,Resistor_SMD:R_0603_1608Metric,False,C22994,Vout = 1.221*(1+10k/3.24k) = 4.99V; R7 C22994 1%
R8,100k,Resistor_SMD:R_0603_1608Metric,False,C25803,
R9,15k,Resistor_SMD:R_0603_1608Metric,False,C22809,External EN divider ~9.4V threshold; stays off at default USB 5V/9V
C4,10u/50V,Capacitor_SMD:C_1206_3216Metric,False,C13585,
C5,10u/50V,Capacitor_SMD:C_1206_3216Metric,False,C13585,
C6,100n/50V,Capacitor_SMD:C_0603_1608Metric,False,C14663,
C7,220u/10V POSCAP,Capacitor_Tantalum_SMD:CP_EIA-7343-40_Kemet-Y,False,C242173,"Panasonic 10TPB220M, 220uF 10V ESR max40mohm; TI reference output capacitor"
C8,47u/10V,Capacitor_SMD:C_1206_3216Metric,True,C96123,
C9,47u/10V,Capacitor_SMD:C_1206_3216Metric,True,C96123,
U3,TLV1117LV33DCYR,Package_TO_SOT_SMD:SOT-223-3_TabPin2,False,C15578,"TI TLV1117LV33: ceramic-output stable, pin-compatible SOT-223"
C10,10u/16V,Capacitor_SMD:C_1206_3216Metric,False,C13585,
C11,22u/10V,Capacitor_SMD:C_1206_3216Metric,False,C12891,
J3,2.54-2*15P,carrier:PinHeader_2x15_Tab5_Bottom,False,C56496,"LCSC C56496 separately purchased; mandatory manual soldering, excluded from PCBA. Bottom mating direction retained."
R10,680R,Resistor_SMD:R_0603_1608Metric,False,C23228,Initial PoC1MHz; DATA setup/hold>=250ns; DIR deadtime>=500ns; weak drive/SLOW. New full-size routing must be re-evaluated.
R11,680R,Resistor_SMD:R_0603_1608Metric,False,C23228,Initial PoC1MHz; DATA setup/hold>=250ns; DIR deadtime>=500ns; weak drive/SLOW. New full-size routing must be re-evaluated.
R12,680R,Resistor_SMD:R_0603_1608Metric,False,C23228,Initial PoC1MHz; DATA setup/hold>=250ns; DIR deadtime>=500ns; weak drive/SLOW. New full-size routing must be re-evaluated.
R13,680R,Resistor_SMD:R_0603_1608Metric,False,C23228,Initial PoC1MHz; DATA setup/hold>=250ns; DIR deadtime>=500ns; weak drive/SLOW. New full-size routing must be re-evaluated.
R14,680R,Resistor_SMD:R_0603_1608Metric,False,C23228,Initial PoC1MHz; DATA setup/hold>=250ns; DIR deadtime>=500ns; weak drive/SLOW. New full-size routing must be re-evaluated.
R15,680R,Resistor_SMD:R_0603_1608Metric,False,C23228,Initial PoC1MHz; DATA setup/hold>=250ns; DIR deadtime>=500ns; weak drive/SLOW. New full-size routing must be re-evaluated.
R16,680R,Resistor_SMD:R_0603_1608Metric,False,C23228,Initial PoC1MHz; DATA setup/hold>=250ns; DIR deadtime>=500ns; weak drive/SLOW. New full-size routing must be re-evaluated.
R17,0R,Resistor_SMD:R_0603_1608Metric,True,C21189,16-bit extension (DNP): connects G37 to FPGA
R18,0R,Resistor_SMD:R_0603_1608Metric,True,C21189,16-bit extension (DNP): connects G38 to FPGA
R19,680R,Resistor_SMD:R_0603_1608Metric,False,C23228,Initial PoC1MHz; DATA setup/hold>=250ns; DIR deadtime>=500ns; weak drive/SLOW. New full-size routing must be re-evaluated.
R20,680R,Resistor_SMD:R_0603_1608Metric,False,C23228,Initial PoC1MHz; DATA setup/hold>=250ns; DIR deadtime>=500ns; weak drive/SLOW. New full-size routing must be re-evaluated.
R21,680R,Resistor_SMD:R_0603_1608Metric,False,C23228,Initial PoC1MHz; DATA setup/hold>=250ns; DIR deadtime>=500ns; weak drive/SLOW. New full-size routing must be re-evaluated.
R22,680R,Resistor_SMD:R_0603_1608Metric,False,C23228,Initial PoC1MHz; DATA setup/hold>=250ns; DIR deadtime>=500ns; weak drive/SLOW. New full-size routing must be re-evaluated.
R23,680R,Resistor_SMD:R_0603_1608Metric,False,C23228,Initial PoC1MHz; DATA setup/hold>=250ns; DIR deadtime>=500ns; weak drive/SLOW. New full-size routing must be re-evaluated.
R24,680R,Resistor_SMD:R_0603_1608Metric,False,C23228,Initial PoC1MHz; DATA setup/hold>=250ns; DIR deadtime>=500ns; weak drive/SLOW. New full-size routing must be re-evaluated.
R25,0R,Resistor_SMD:R_0603_1608Metric,True,C21189,16-bit extension (DNP): connects G35 to FPGA
R26,680R,Resistor_SMD:R_0603_1608Metric,False,C23228,Initial PoC1MHz; DATA setup/hold>=250ns; DIR deadtime>=500ns; weak drive/SLOW. New full-size routing must be re-evaluated.
R27,680R,Resistor_SMD:R_0603_1608Metric,False,C23228,Initial PoC1MHz; DATA setup/hold>=250ns; DIR deadtime>=500ns; weak drive/SLOW. New full-size routing must be re-evaluated.
J4,SOCKET XDAP-4042044-20401,carrier:DDR3_XDAP_4042044_20401,False,C22471982,"PCBA mandatory; socket only, Core module supplied by user; confirm stock/fixture"
J5,HDMI OUT,Connector_Video:HDMI_A_Molex_208658-1001_Horizontal,False,C916313,MOLEX 2086581001; PCBA required including four through-hole shell tabs; no customer HDMI soldering. Confirm full connector assembly in supplier preview.
C12,100n,Capacitor_SMD:C_0402_1005Metric,False,C1525,100nF AC coupling; low-profile 0402 under Core
R28,499R,Resistor_SMD:R_0603_1608Metric,False,C23065,
C13,100n,Capacitor_SMD:C_0402_1005Metric,False,C1525,100nF AC coupling; low-profile 0402 under Core
R29,499R,Resistor_SMD:R_0603_1608Metric,False,C23065,
C14,100n,Capacitor_SMD:C_0402_1005Metric,False,C1525,100nF AC coupling; low-profile 0402 under Core
R30,499R,Resistor_SMD:R_0402_1005Metric,False,C4125,
C15,100n,Capacitor_SMD:C_0402_1005Metric,False,C1525,100nF AC coupling; low-profile 0402 under Core
R31,499R,Resistor_SMD:R_0402_1005Metric,False,C4125,
C16,100n,Capacitor_SMD:C_0402_1005Metric,False,C1525,100nF AC coupling; low-profile 0402 under Core
R32,499R,Resistor_SMD:R_0603_1608Metric,False,C23065,
C17,100n,Capacitor_SMD:C_0402_1005Metric,False,C1525,100nF AC coupling; low-profile 0402 under Core
R33,499R,Resistor_SMD:R_0603_1608Metric,False,C23065,
C18,100n,Capacitor_SMD:C_0402_1005Metric,False,C1525,100nF AC coupling; low-profile 0402 under Core
R34,499R,Resistor_SMD:R_0603_1608Metric,False,C23065,
C19,100n,Capacitor_SMD:C_0402_1005Metric,False,C1525,100nF AC coupling; low-profile 0402 under Core
R35,499R,Resistor_SMD:R_0603_1608Metric,False,C23065,
U4,RCLAMP0524P,carrier:DFN2510-10L_RCLAMP0524P,False,C293965,"TMDS ESD array (DOWO DFN2510-10L): I/O 1,2,4,5, GND 3,8; the line is routed as continuous copper through strapped pads"
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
